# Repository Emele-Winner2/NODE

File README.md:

# NODE IO BOARD

The **NODE IO BOARD** is an embedded hardware node featuring an **ESP32-C3** microcontroller, onboard environmental and motion sensors, USB-C power/data delivery, and external micro-SD card storage. It serves as a compact, all-in-one sensor node designed for IoT applications, environmental monitoring, and motion tracking.

---

## Technical Specifications

### 1. Main Controller

* **MCU:** ESP32-C3-MINI-1 / ESP32-C3-MINI-2 module (RISC-V single-core processor).

* **Auto-Flash/Reset Circuitry:** Dual NPN transistor circuit (DTR/RTS) for automatic bootloader entry and flashing over USB.

* **Tactile Switches:** Dedicated `RESET` and `BOOT` push buttons.

### 2. Power Supply

* **Power Input:** USB Type-C Receptacle (USB 2.0 interface) or external 5V input header (`J2`).

* **ESD Protection:** Dedicated ESD protection diodes (`ESD9B5.0ST5G`) across VBUS, D+, and D- lines.

* **Voltage Regulation:** Onboard **LD1117S33TR** LDO regulator stepping down 5V (VBUS) to 3.3V for MCU and sensor power rails.

### 3. USB to UART Bridge

* **Bridge IC:** **CP2102N** (QFN-28) USB-to-UART bridge controller.

* Communicates directly with the ESP32-C3 via `U0RXD` and `U0TXD` pins.

### 4. Onboard Sensors & Peripherals

* **Environmental Sensor:** **BME688** gas, temperature, pressure, and humidity sensor connected over I²C (`SCL`, `SDA`).

* **Inertial Measurement Unit (IMU):** **BMI323** 6-axis IMU connected via I²C (`SCL`, `SDA`) with dedicated interrupt lines (`BMI_INT1`, `BMI_INT2`).

* **MicroSD Card Slot:** SPI-driven SD card slot (`MEM2067`) connected via SPI lines (`SPI_CLK`, `MOSI`, `MISO`, `SPI_CS`) for local data logging.

---

## Block Diagram Overview

```text
               +-----------------------+
               |  USB-C / 5V Header    |
               +-----------+-----------+
                           |
            +--------------+--------------+
            |                             |
    +-------v-------+             +-------v-------+
    | 3.3V LDO      |             | CP2102N USB-  |
    | (LD1117S33)   |             | to-UART Bridge|
    +-------+-------+             +-------+-------+
            |                             |
            +--------------+--------------+
                           |
                 +---------v---------+
                 |    ESP32-C3       |
                 |  Microcontroller  |
                 +----+----+----+----+
                      |    |    |
       +--------------+    |    +---------------+
       | I2C               | SPI                | Interrupts / Controls
+------v-------+    +------v-------+    +-------v------+
|   BME688     |    |  MicroSD     |    | Boot & Reset |
| Env Sensor   |    | Card Slot    |    |   Buttons    |
+--------------+    +--------------+    +--------------+
|   BMI323     |
|  6-Axis IMU  |
+--------------+

```

## Project Design Files

This hardware project was designed in **KiCad 10.0**:

* `NODE IO BOARD.kicad_sch` — Schematic source file

* Hardware revision: **Rev 1.0**

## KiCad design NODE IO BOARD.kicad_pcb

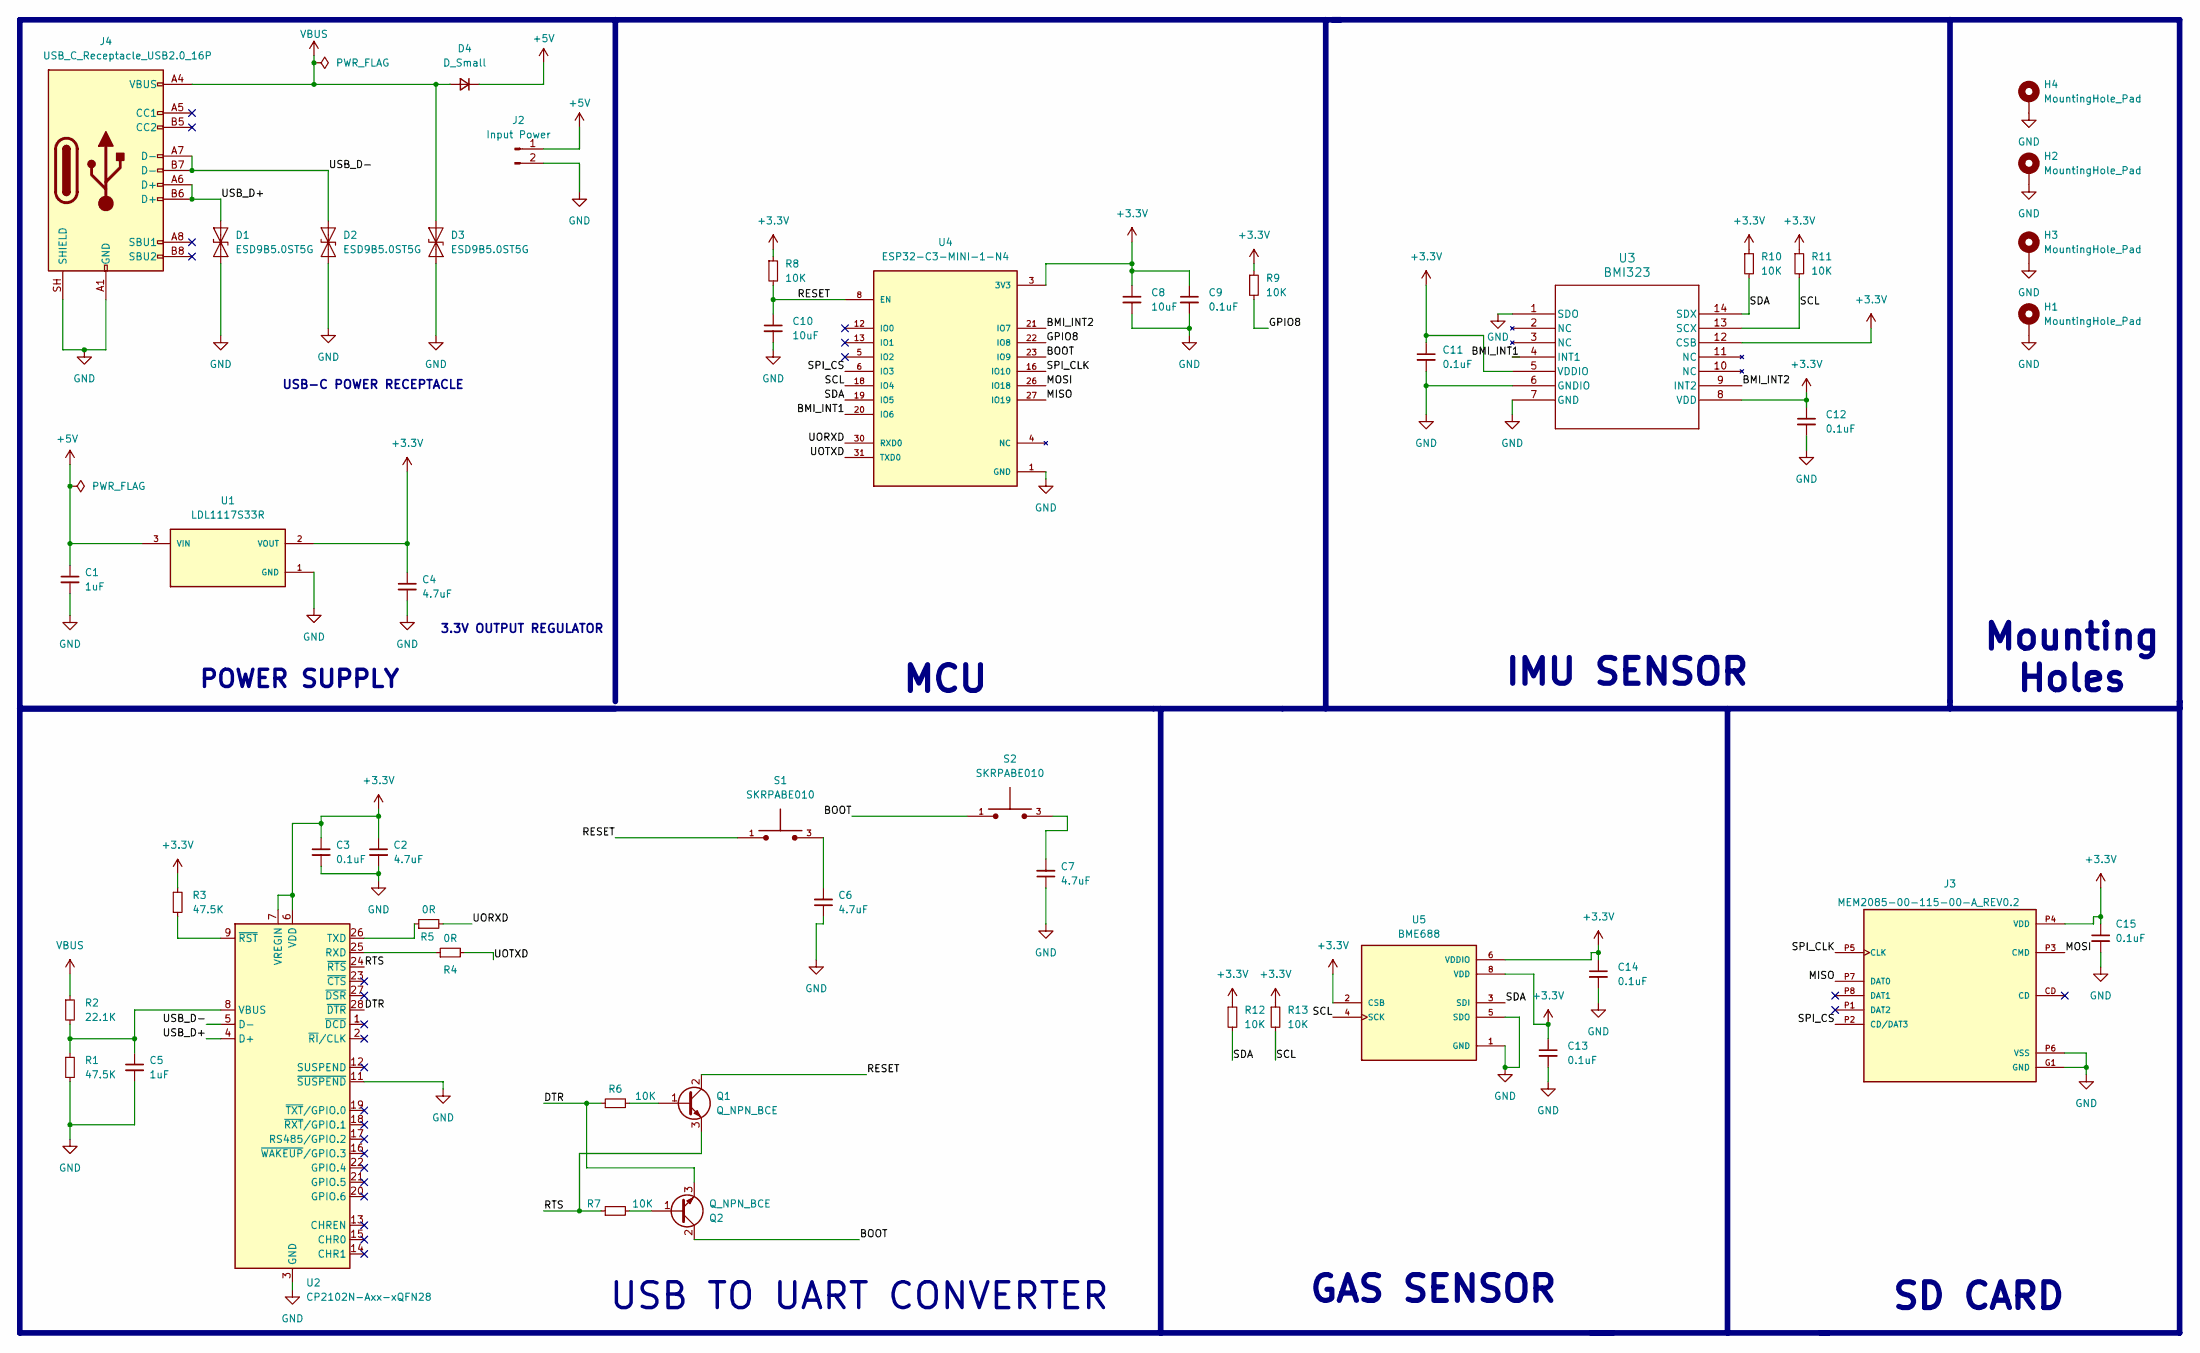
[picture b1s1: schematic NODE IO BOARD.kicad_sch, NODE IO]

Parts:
C1, C5: 1uF; C_0603_1608Metric
C2, C4, C6, C7: 4.7uF; C_0603_1608Metric
C3, C9, C11, C12, C13, C14, C15: 0.1uF; C_0603_1608Metric
C8, C10: 10uF; C_0603_1608Metric
D1, D2, D3: ESD9B5.0ST5G; D_SOD-923
D4: D_Small; D_SOD-123
H1, H2, H3, H4: MountingHole_Pad; MountingHole_2.5mm_Pad
J2: Input Power; JST_EH_S2B-EH_1x02_P2.50mm_Horizontal
J3: MEM2085-00-115-00-A_REV0.2; GCT_MEM2085-00-115-00-A_REV0.2; PARTREV 0.2
J4: USB_C_Receptacle_USB2.0_16P; USB_C_Receptacle_GCT_USB4105-xx-A_16P_TopMnt_Horizontal
Q1, Q2: Q_NPN_BCE; TSOT-23
R1, R3: 47.5K; R_0603_1608Metric
R2: 22.1K; R_0603_1608Metric
R4, R5: 0R; R_0603_1608Metric
R6, R7, R8, R9, R10, R11, R12, R13: 10K; R_0603_1608Metric
S1, S2: SKRPABE010; SW_SKRPABE010
U1: LDL1117S33R; SOT230P700X180-4N; PARTREV 7
U2: CP2102N-Axx-xQFN28; QFN50P500X500X100-29N
U3: BMI323; BMI323_BOS
U4: ESP32-C3-MINI-1-N4; XCVR_ESP32-C3-MINI-1-N4; PARTREV v1.0
U5: BME688; IC_BME688; PARTREV 1.0

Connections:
+3.3V: C2.1, C3.1, C4.1, C8.1, C9.1, C11.1, C12.1, C13.1, C14.1, C15.1, J3.P4 (VDD), R3.1, R8.1, R9.1, R10.1, R11.1, R12.1, R13.1, U1.2 (VOUT), U1.4 (VOUT), U2.6 (VDD), U2.7 (VREGIN), U3.5 (VDDIO), U3.8 (VDD), U3.12 (CSB), U4.3 (3V3), U5.2 (CSB), U5.6 (VDDIO), U5.8 (VDD)
+5V: C1.1, D4.1 (K), J2.1, U1.3 (VIN)
/BMI_INT1: U3.4 (INT1), U4.20 (IO6)
/BMI_INT2: U3.9 (INT2), U4.21 (IO7)
/BOOT: Q2.2 (C), S2.1, S2.2, U4.23 (IO9)
/DTR: Q2.3 (E), R6.1, U2.28 (~DTR)
/GPIO8: R9.2, U4.22 (IO8)
/MISO: J3.P7 (DAT0), U4.27 (IO19)
/MOSI: J3.P3 (CMD), U4.26 (IO18)
/RESET: C10.1, Q1.2 (C), R8.2, S1.1, S1.2, U4.8 (EN)
/RTS: Q1.3 (E), R7.1, U2.24 (~RTS)
/SCL: R11.2, R13.2, U3.13 (SCX), U4.18 (IO4), U5.4 (SCK)
/SDA: R10.2, R12.2, U3.14 (SDX), U4.19 (IO5), U5.3 (SDI)
/SPI_CLK: J3.P5 (CLK), U4.16 (IO10)
/SPI_CS: J3.P2 (CD/DAT3), U4.6 (IO3)
/UORXD: R5.2, U4.30 (RXD0)
/UOTXD: R4.2, U4.31 (TXD0)
/USB_D+: D1.2 (A2), J4.A6 (D+), J4.B6 (D+), U2.4 (D+)
/USB_D-: D2.2 (A2), J4.A7 (D-), J4.B7 (D-), U2.5 (D-)
GND: C1.2, C2.2, C3.2, C4.2, C5.2, C6.1, C7.1, C8.2, C9.2, C10.2, C11.2, C12.2, C13.2, C14.2, C15.2, D1.1 (A1), D2.1 (A1), D3.1 (A1), H1.1 (1_1), H2.1 (1_1), H3.1 (1_1), H4.1 (1_1), J2.2, J3.G1 (GND), J3.G2 (GND), J3.G3 (GND), J3.G4 (GND), J3.G5 (GND), J3.G6 (GND), J3.G7 (GND), J3.G8 (GND), J3.G9 (GND), J3.G10 (GND), J3.P6 (VSS), J4.A1 (GND), J4.A12 (GND), J4.B1 (GND), J4.B12 (GND), J4.SH (SHIELD), R1.2, U1.1 (GND), U2.3 (GND), U2.11 (~SUSPEND), U2.29 (GND), U3.1 (SDO), U3.6 (GNDIO), U3.7 (GND), U4.1 (GND), U4.2 (GND), U4.11 (GND), U4.14 (GND), U4.36 (GND), U4.37 (GND), U4.38 (GND), U4.39 (GND), U4.40 (GND), U4.41 (GND), U4.42 (GND), U4.43 (GND), U4.44 (GND), U4.45 (GND), U4.46 (GND), U4.47 (GND), U4.48 (GND), U4.49_1 (GND), U4.49_2 (GND), U4.49_3 (GND), U4.49_4 (GND), U4.49_5 (GND), U4.49_6 (GND), U4.49_7 (GND), U4.49_8 (GND), U4.49_9 (GND), U4.50 (GND), U4.51 (GND), U4.52 (GND), U4.53 (GND), U5.1 (GND), U5.5 (SDO), U5.7 (GND)
unnamed: C6.2, S1.3, S1.4
unnamed: C7.2, S2.3, S2.4
unnamed: Q1.1 (B), R6.2
unnamed: Q2.1 (B), R7.2
unnamed: R4.1, U2.25 (RXD)
unnamed: R5.1, U2.26 (TXD)
unnamed: C5.1, R1.1, R2.2, U2.8 (VBUS)
unnamed: R3.2, U2.9 (~RST)
VBUS: D3.2 (A2), D4.2 (A), J4.A4 (VBUS), J4.A9 (VBUS), J4.B4 (VBUS), J4.B9 (VBUS), R2.1

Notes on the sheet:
USB-C POWER RECEPTACLE
Mounting Holes
SD CARD
IMU SENSOR
MCU
GAS SENSOR
USB TO UART CONVERTER
3.3V OUTPUT REGULATOR
POWER SUPPLY

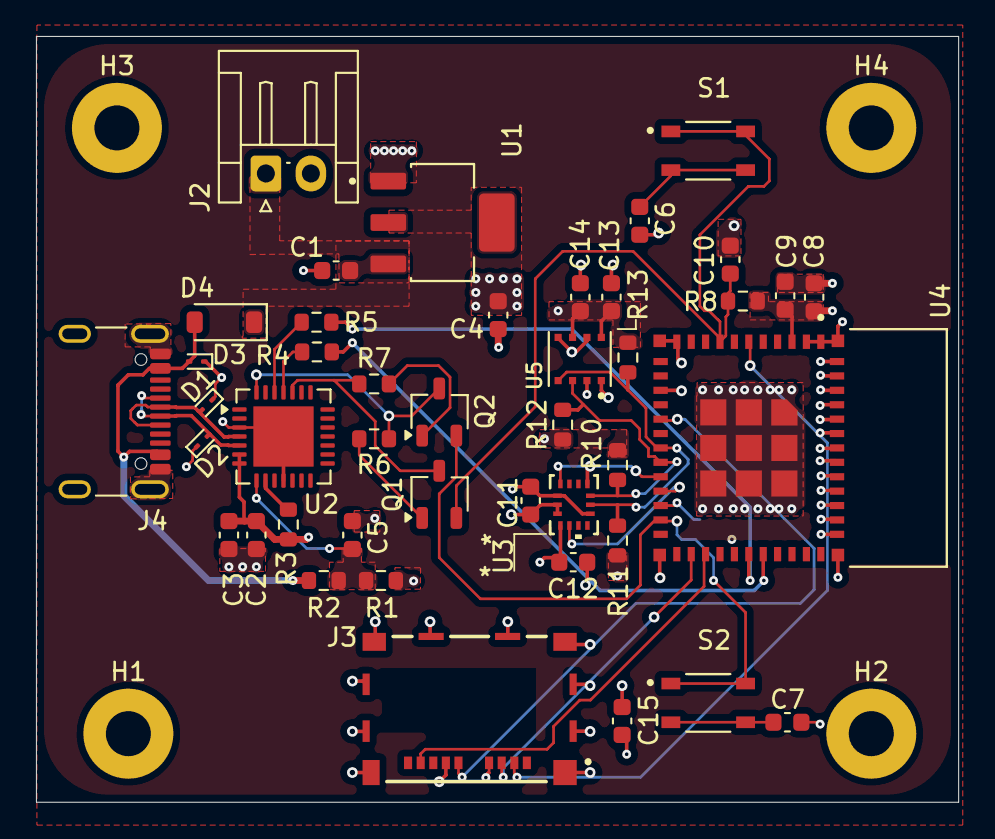
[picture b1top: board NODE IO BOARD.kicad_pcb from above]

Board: 4 copper layers, 51.2 x 42.5 mm, 48 parts (1 on the bottom side), 29 nets.
